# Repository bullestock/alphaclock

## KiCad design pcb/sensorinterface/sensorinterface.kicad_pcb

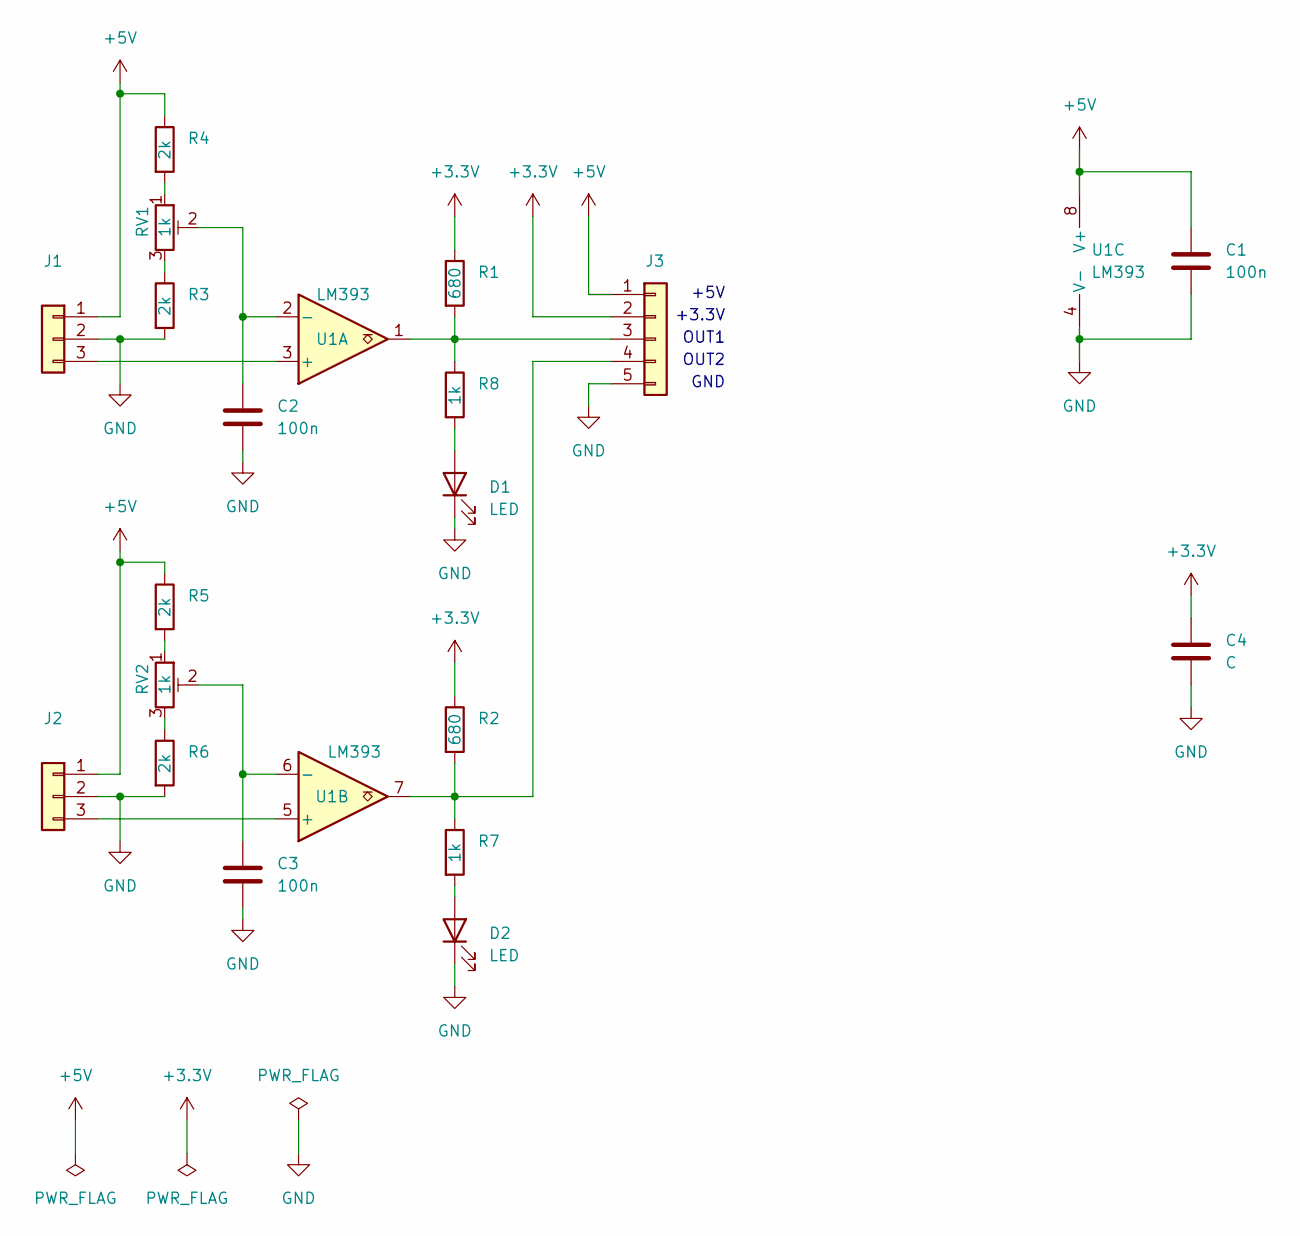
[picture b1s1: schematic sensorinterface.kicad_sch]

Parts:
C1, C2, C3: 100n; C_0603_1608Metric
C4: C; C_0603_1608Metric
D1, D2: LED; LED_0603_1608Metric
J1, J2: Conn_01x03; JST_XH_B3B-XH-A_1x03_P2.50mm_Vertical
J3: Conn_01x05; JST_XH_B5B-XH-A_1x05_P2.50mm_Vertical
R1, R2: 680; R_0603_1608Metric
R3, R4, R5, R6: 2k; R_0603_1608Metric
R7, R8: 1k; R_0603_1608Metric
RV1, RV2: 1k; Potentiometer_Trimmer_ACP_CA6v_Horizontal
U1: LM393; DIP-8_W7.62mm

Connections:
+3.3V: C4.1, J3.2, R1.1, R2.1
+5V: C1.1, J1.1, J2.1, J3.1, R4.1, R5.1, U1.8 (V+)
GND: C1.2, C2.2, C3.2, C4.2, D1.1 (K), D2.1 (K), J1.2, J2.2, J3.5, R3.2, R6.2, U1.4 (V-)
unnamed: D1.2 (A), R8.2
unnamed: D2.2 (A), R7.2
unnamed: J1.3, U1.3 (+)
unnamed: J2.3, U1.5 (+)
unnamed: J3.3, R1.2, R8.1, U1.1
unnamed: J3.4, R2.2, R7.1, U1.7
unnamed: R3.1, RV1.3
unnamed: R4.2, RV1.1
unnamed: R5.2, RV2.1
unnamed: R6.1, RV2.3
unnamed: C2.1, RV1.2, U1.2 (-)
unnamed: C3.1, RV2.2, U1.6 (-)

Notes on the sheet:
GND
+5V
OUT2
+3.3V
OUT1

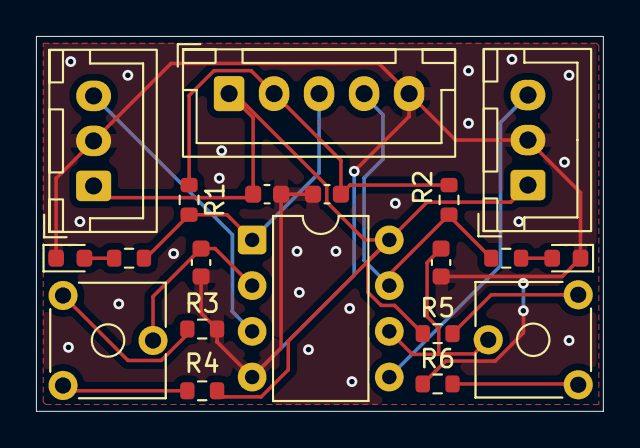
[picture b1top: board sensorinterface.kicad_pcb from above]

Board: 2 copper layers, 31.5 x 20.8 mm, 20 parts (0 on the bottom side), 15 nets.

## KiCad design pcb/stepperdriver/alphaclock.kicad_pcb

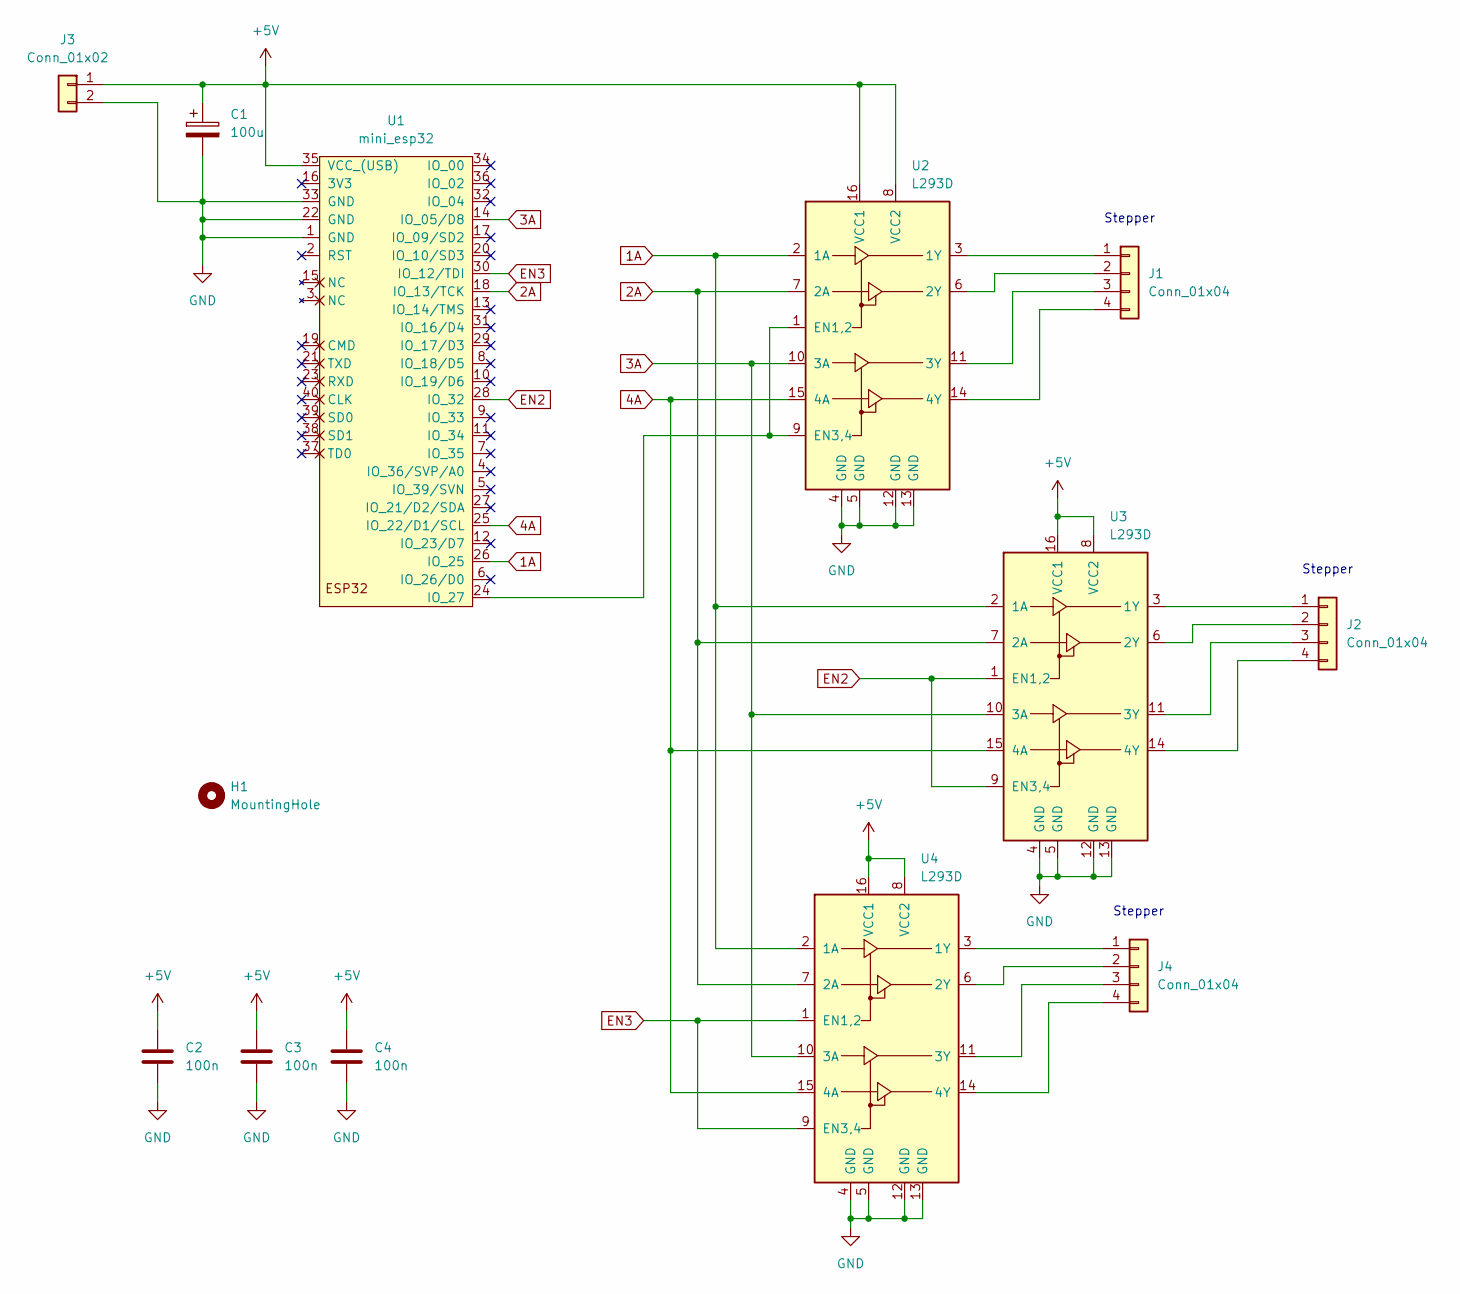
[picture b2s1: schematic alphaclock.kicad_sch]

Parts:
C1: 100u; CP_Elec_10x10
C2, C3, C4: 100n; C_0603_1608Metric
H1: MountingHole; MountingHole_3.2mm_M3
J1, J2, J4: Conn_01x04; JST_XH_B4B-XH-A_1x04_P2.50mm_Vertical
J3: Conn_01x02; JST_XH_B2B-XH-A_1x02_P2.50mm_Vertical
U1: mini_esp32; ESP32_mini
U2, U3, U4: L293D; DIP-16_W7.62mm

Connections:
1A: U1.26 (IO_25), U2.2 (1A), U3.2 (1A), U4.2 (1A)
2A: U1.18 (IO_13/TCK), U2.7 (2A), U3.7 (2A), U4.7 (2A)
3A: U1.14 (IO_05/D8), U2.10 (3A), U3.10 (3A), U4.10 (3A)
4A: U1.25 (IO_22/D1/SCL), U2.15 (4A), U3.15 (4A), U4.15 (4A)
+5V: C1.1, C2.1, C3.1, C4.1, J3.1, U1.35 (VCC_(USB)), U2.8 (VCC2), U2.16 (VCC1), U3.8 (VCC2), U3.16 (VCC1), U4.8 (VCC2), U4.16 (VCC1)
EN2: U1.28 (IO_32), U3.1 (EN1,2), U3.9 (EN3,4)
EN3: U1.30 (IO_12/TDI), U4.1 (EN1,2), U4.9 (EN3,4)
GND: C1.2, C2.2, C3.2, C4.2, J3.2, U1.1 (GND), U1.22 (GND), U1.33 (GND), U2.4 (GND), U2.5 (GND), U2.12 (GND), U2.13 (GND), U3.4 (GND), U3.5 (GND), U3.12 (GND), U3.13 (GND), U4.4 (GND), U4.5 (GND), U4.12 (GND), U4.13 (GND)
unnamed: J1.1, U2.3 (1Y)
unnamed: J1.2, U2.6 (2Y)
unnamed: J1.3, U2.11 (3Y)
unnamed: J1.4, U2.14 (4Y)
unnamed: J2.1, U3.3 (1Y)
unnamed: J2.2, U3.6 (2Y)
unnamed: J2.3, U3.11 (3Y)
unnamed: J2.4, U3.14 (4Y)
unnamed: J4.1, U4.3 (1Y)
unnamed: J4.2, U4.6 (2Y)
unnamed: J4.3, U4.11 (3Y)
unnamed: J4.4, U4.14 (4Y)
unnamed: U1.24 (IO_27), U2.1 (EN1,2), U2.9 (EN3,4)

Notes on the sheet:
Stepper

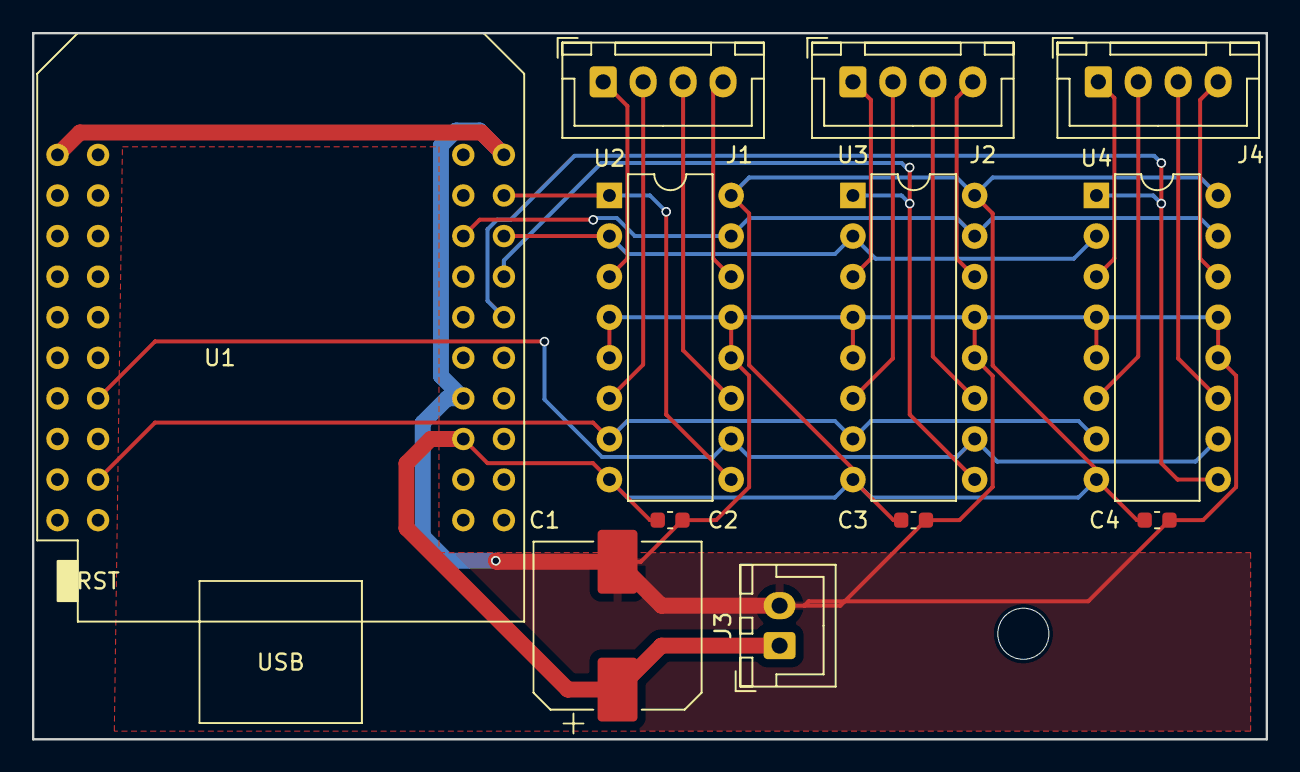
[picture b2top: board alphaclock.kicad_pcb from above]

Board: 2 copper layers, 77.2 x 44.2 mm, 13 parts (0 on the bottom side), 21 nets.

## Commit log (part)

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2024-12-22 Add skeleton esp-idf project.
2024-12-22 Add clock face.
2024-12-22 Add standard code.
2024-12-22 Add stepper control.
2024-12-22 Add schematic.
2024-12-23 Swap IO16/17 and IO18/19 for easier layout.
2024-12-25 Remove pin numbers from ctor, update pins, add enable pin.
2024-12-25 Use interrupt.
2025-01-30 Add missing libraries.
2025-02-08 Complete routing
2025-02-08 Update code to match PCB
2025-02-09 Order.
2025-02-16 Gears for hour hand.
2025-02-16 First attempt.
2025-02-16 Tweak.
2025-02-17 Rename.
2025-02-21 Support structure for gear wheels, lower part.
2025-02-23 Add support for 3 motors.
2025-02-26 Add dots to decrease friction.
2025-02-26 Add motor test command. Make stepper 1 work.
2025-03-03 Add websocket echo server.
2025-03-21 Decrease friction.
2025-03-21 Holder for 20 mm steppers.
2025-03-21 Add Stepper::busy().
2025-03-22 Holders for steppers.
2025-03-22 Holder for seconds stepper, part 2.
2025-03-22 Holder for seconds stepper, part 1.
2025-03-23 WIP: Implement microstepping.
2025-03-23 Refine microstepping.
2025-03-28 Try with pulleys.
2025-04-15 Add frontend skeleton.
2025-04-16 Add HTML/JS files.
2025-04-16 Make buttons send WS commands.
2025-04-16 Handle button WS commands.
2025-04-16 Fix stepping.
2025-04-17 Add touch compatibility.
2025-04-17 Cleanup.
2025-04-17 Rework stepper handling.
2025-04-17 Handle pointerout events.
2025-05-06 Make all buttons work.
2025-05-06 Simplify.
2025-07-19 First attempt (does not print properly).
2025-07-19 Add pulley.
2025-07-20 Mount for bearing.
2025-07-22 Add stuff.
2025-07-23 Quarter ring.
2025-07-23 Add 'fast' buttons.
2025-07-26 Add calibration mechanism.
2025-07-27 Increase pulley sizze for better resolution.
2025-07-27 Improve.
2025-07-28 Rename, delete old stuff.
2025-08-13 Enlarge pulleys.
2025-08-13 Fix bugs.
2025-08-25 Refactor.
2025-08-25 Add mode control.
2025-08-30 Fix bug.
2025-08-30 Set timezone.
2025-08-30 Implement normal and fast mode.
2025-08-30 Implement hour mapping.
2025-08-30 Implement hour mode.
2025-08-30 Clean up debug.
2025-08-31 Add zero buttons.
2025-10-04 Add motor mount.
2025-10-06 Make motors go the right way round.
2025-10-06 Hack pulley so that JLC can print it.
2025-10-07 Handle wraparound.
2025-10-07 Fix #ifdef.
2025-10-07 Increase precision of displayed calibration data.
2025-10-10 Start adapting for using gears.
2025-10-21 Update hole diameter.
2025-10-21 Make crush ribs bigger.
2025-10-25 First version.
2025-11-10 Simple round spacer for 2 mm axle.
2025-11-10 Enlarge hole.
2025-11-10 Coupler for connecting 2 mm axle and 1.5 mm motor axle.
2025-11-10 Add insert holes.
2025-11-19 Update for gear wheels.
2025-11-19 Add new stuff.
2025-11-25 Tweak
2025-11-28 Add insert holes for top part.
2025-11-28 Reduce insert hole size.
2025-11-28 Fix insert hole positions.
2025-12-02 Work.
2025-12-06 Tweaks.
2025-12-06 Add go to zero buttons; increase speed.
2025-12-07 Move seconds hand first.
2025-12-07 Add 'motor debug' NVS setting.
2025-12-07 Add 'motor delay' NVS setting.
2025-12-07 Add 'hands' command.
2025-12-07 Add 'transition' command.
2025-12-14 If no args, print current delay.
2025-12-14 Start porting to MKS DLC32.
2026-01-10 Fix I2S pin numbers.
2026-01-10 Use a FSA to ensure that STEP is kept high long enough.
2026-01-11 Add mount for MKS DLOC32 board.
2026-01-17 Require multiple keypresses to enter debug mode.
2026-01-17 Make set_hands() move in parallel.
2026-01-18 Integrate display.
2026-04-30 Fix IP display.
2026-06-29 Add sensor support; update for ESP-IDF 6.
